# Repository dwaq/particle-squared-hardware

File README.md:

# Particle Squared - Bare Bones

This is a forked version of [Jared Wolff's Particle Squared Hardware](https://bitbucket.org/circuitdojo/particle-squared-hardware). For more information on that board, [visit his website](https://www.jaredwolff.com/particle-squared-air-quality-sensor/). To support him and his work, you can  [order his sensors from here](https://www.jaredwolff.com/store/particle-squared/).

Particle^2 (pronounced Particle Squared) is a circuit board that helps you monitor the air quality around you. I call my fork of the project "Bare Bones" because I removed the air particulate sensor. It can still monitor humidity, temperature, eCO2 and TVOCs.

I also made some minor changes to the project to suit my goals.

This project was designed using Autodesk Eagle.

The [Eagle-Renders](/Eagle-Renders) directory contains PDF and PNG renders of the schematic and board layout.

[Here is a shared project on Mouser for the BOM for one PCB.](https://www.mouser.com/ProjectManager/ProjectDetail.aspx?AccessID=5dd38de383)

## License

The license for these files is: [Attribution-ShareAlike 4.0 International](https://creativecommons.org/licenses/by-sa/4.0/). See included `LICENSE` file for all the legal stuff.

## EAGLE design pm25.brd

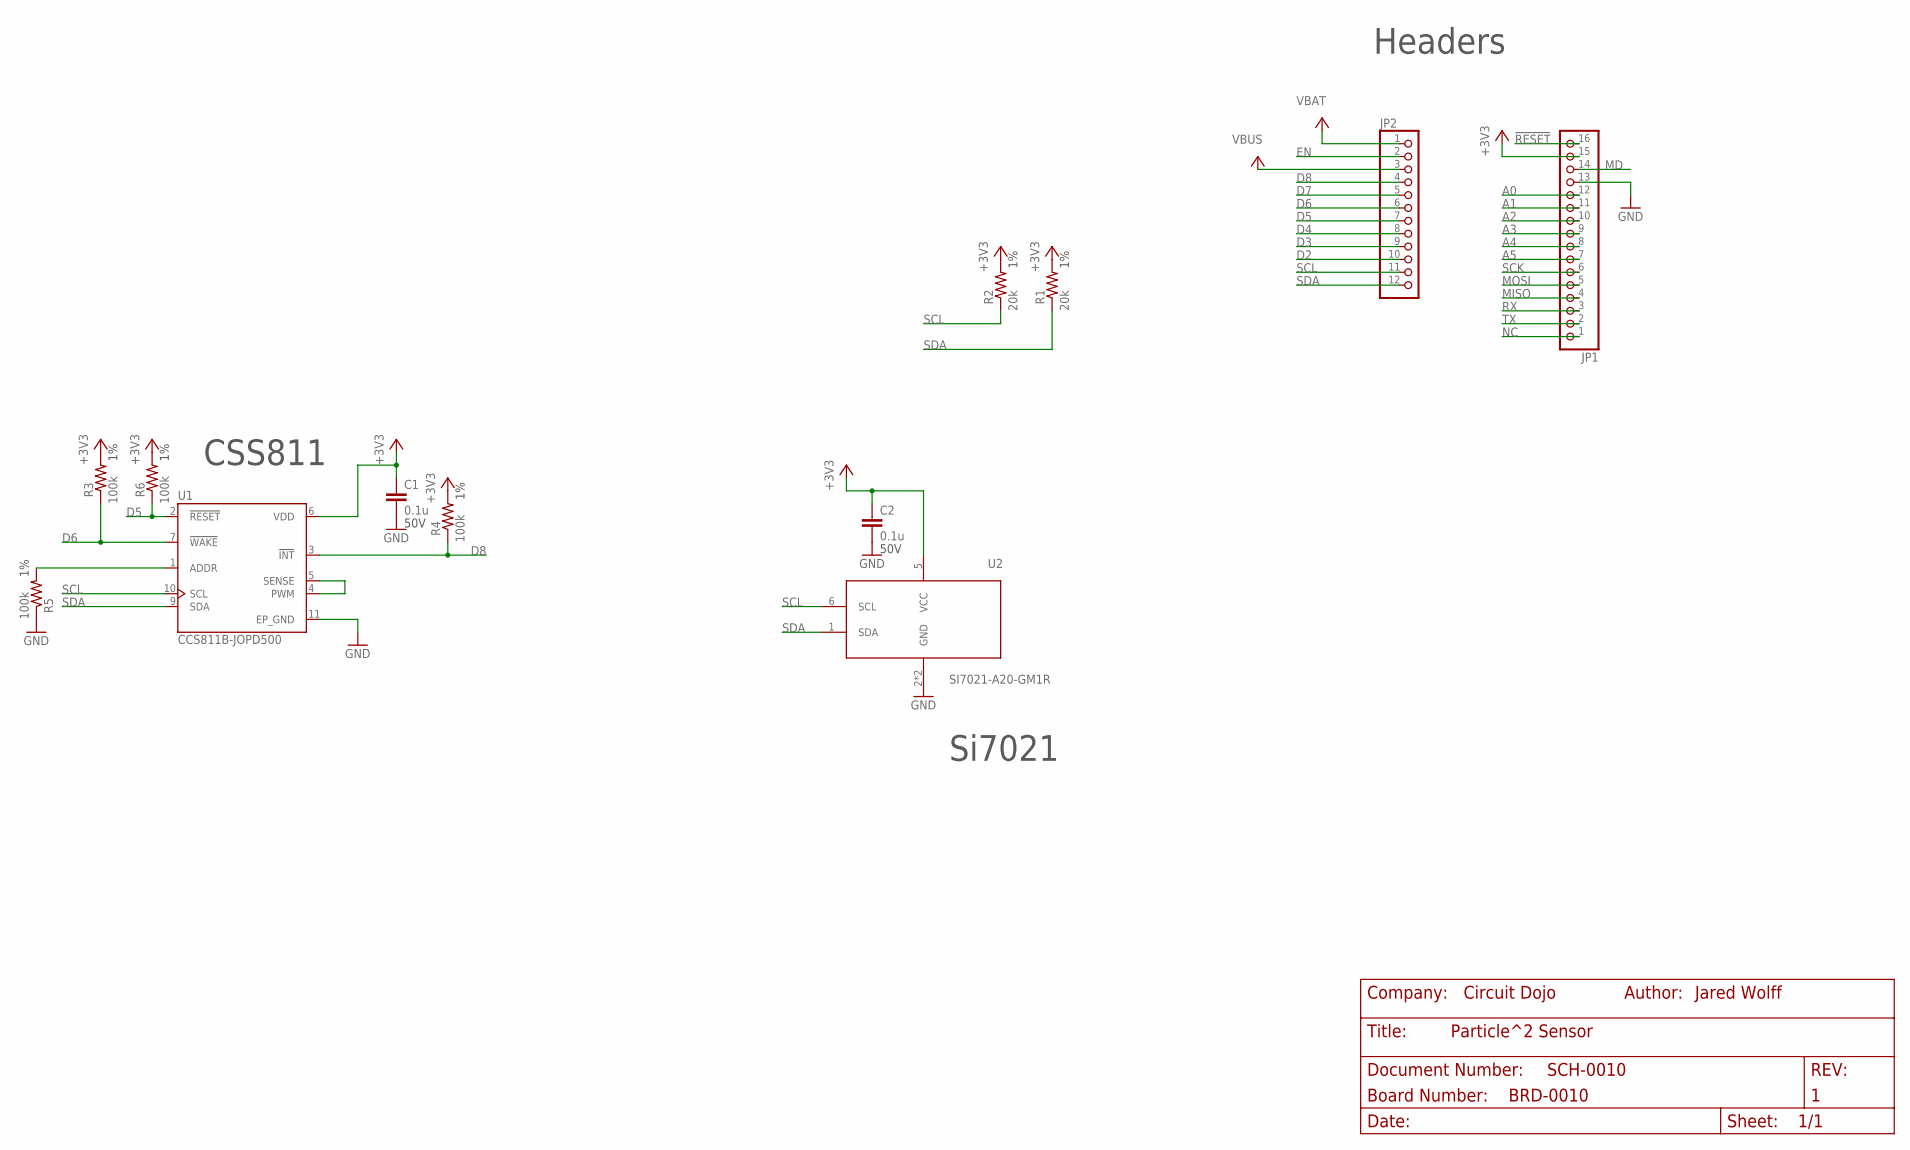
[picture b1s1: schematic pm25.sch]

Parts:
C1, C2: 0.1u; CAPC1005X55N
JP1: HEADER-1X16ROUND; 1X16_ROUND; MPN PPPC161LFBN-RC
JP2: HEADER-1X12; 1X12_ROUND; MPN PPPC121LFBN-RC
R1, R2: 20k; R0402
R3, R4, R5, R6: 100k; R0402
U1: CCS811B-JOPD500; SON60P400X270X110-11N
U2: SI7021-A20-GM1R; SON100P300X300X80-7N

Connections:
!RESET: JP1.16
+3V3: C1.1, C2.1, JP1.15, R1.2, R2.2, R3.2, R4.2, R6.2, U1.6 (VDD), U2.5 (VCC)
A0: JP1.12
A1: JP1.11
A2: JP1.10
A3: JP1.9
A4: JP1.8
A5: JP1.7
D2: JP2.10
D3: JP2.9
D4: JP2.8
D5: JP2.7, R6.1, U1.2 (!RESET)
D6: JP2.6, R3.1, U1.7 (!WAKE)
D7: JP2.5
D8: JP2.4, R4.1, U1.3 (!INT)
EN: JP2.2
GND: C1.2, C2.2, JP1.13, R5.1, U1.11 (EP_GND), U2.2 (GND), U2.7 (GND)
MD: JP1.14
MISO: JP1.4
MOSI: JP1.5
unnamed: R5.2, U1.1 (ADDR)
unnamed: U1.4 (PWM), U1.5 (SENSE)
NC: JP1.1
RX: JP1.3
SCK: JP1.6
SCL: JP2.11, R2.1, U1.10 (SCL), U2.6 (SCL)
SDA: JP2.12, R1.1, U1.9 (SDA), U2.1 (SDA)
TX: JP1.2
VBAT: JP2.1
VBUS: JP2.3

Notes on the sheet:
Si7021
CSS811
Headers

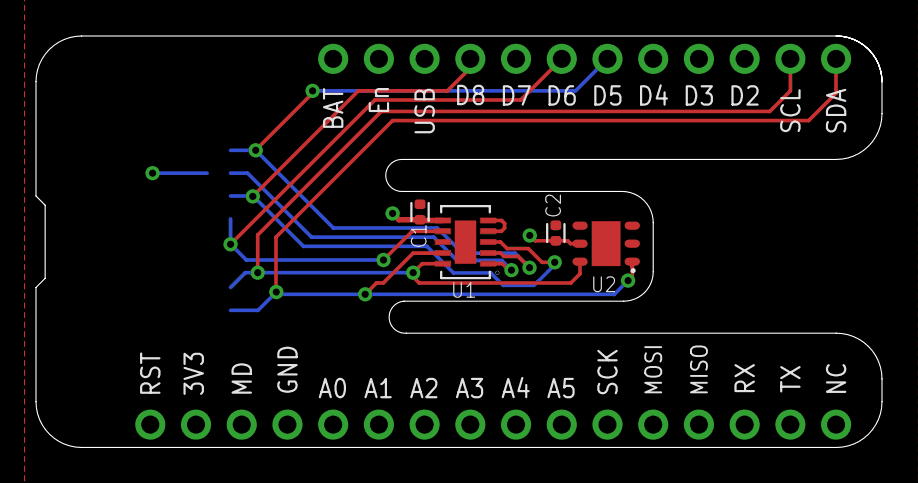
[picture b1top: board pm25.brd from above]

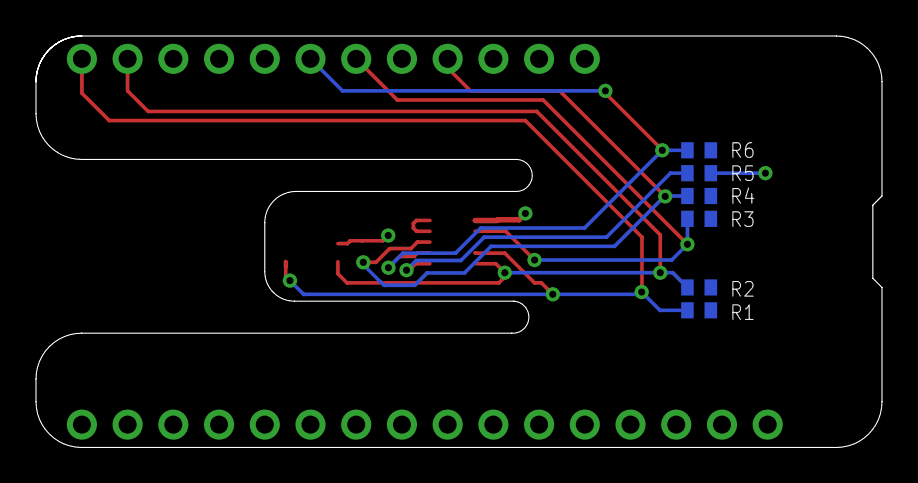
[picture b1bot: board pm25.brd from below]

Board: 2 copper layers, 47.0 x 22.9 mm, 12 parts (6 on the bottom side), 9 nets.

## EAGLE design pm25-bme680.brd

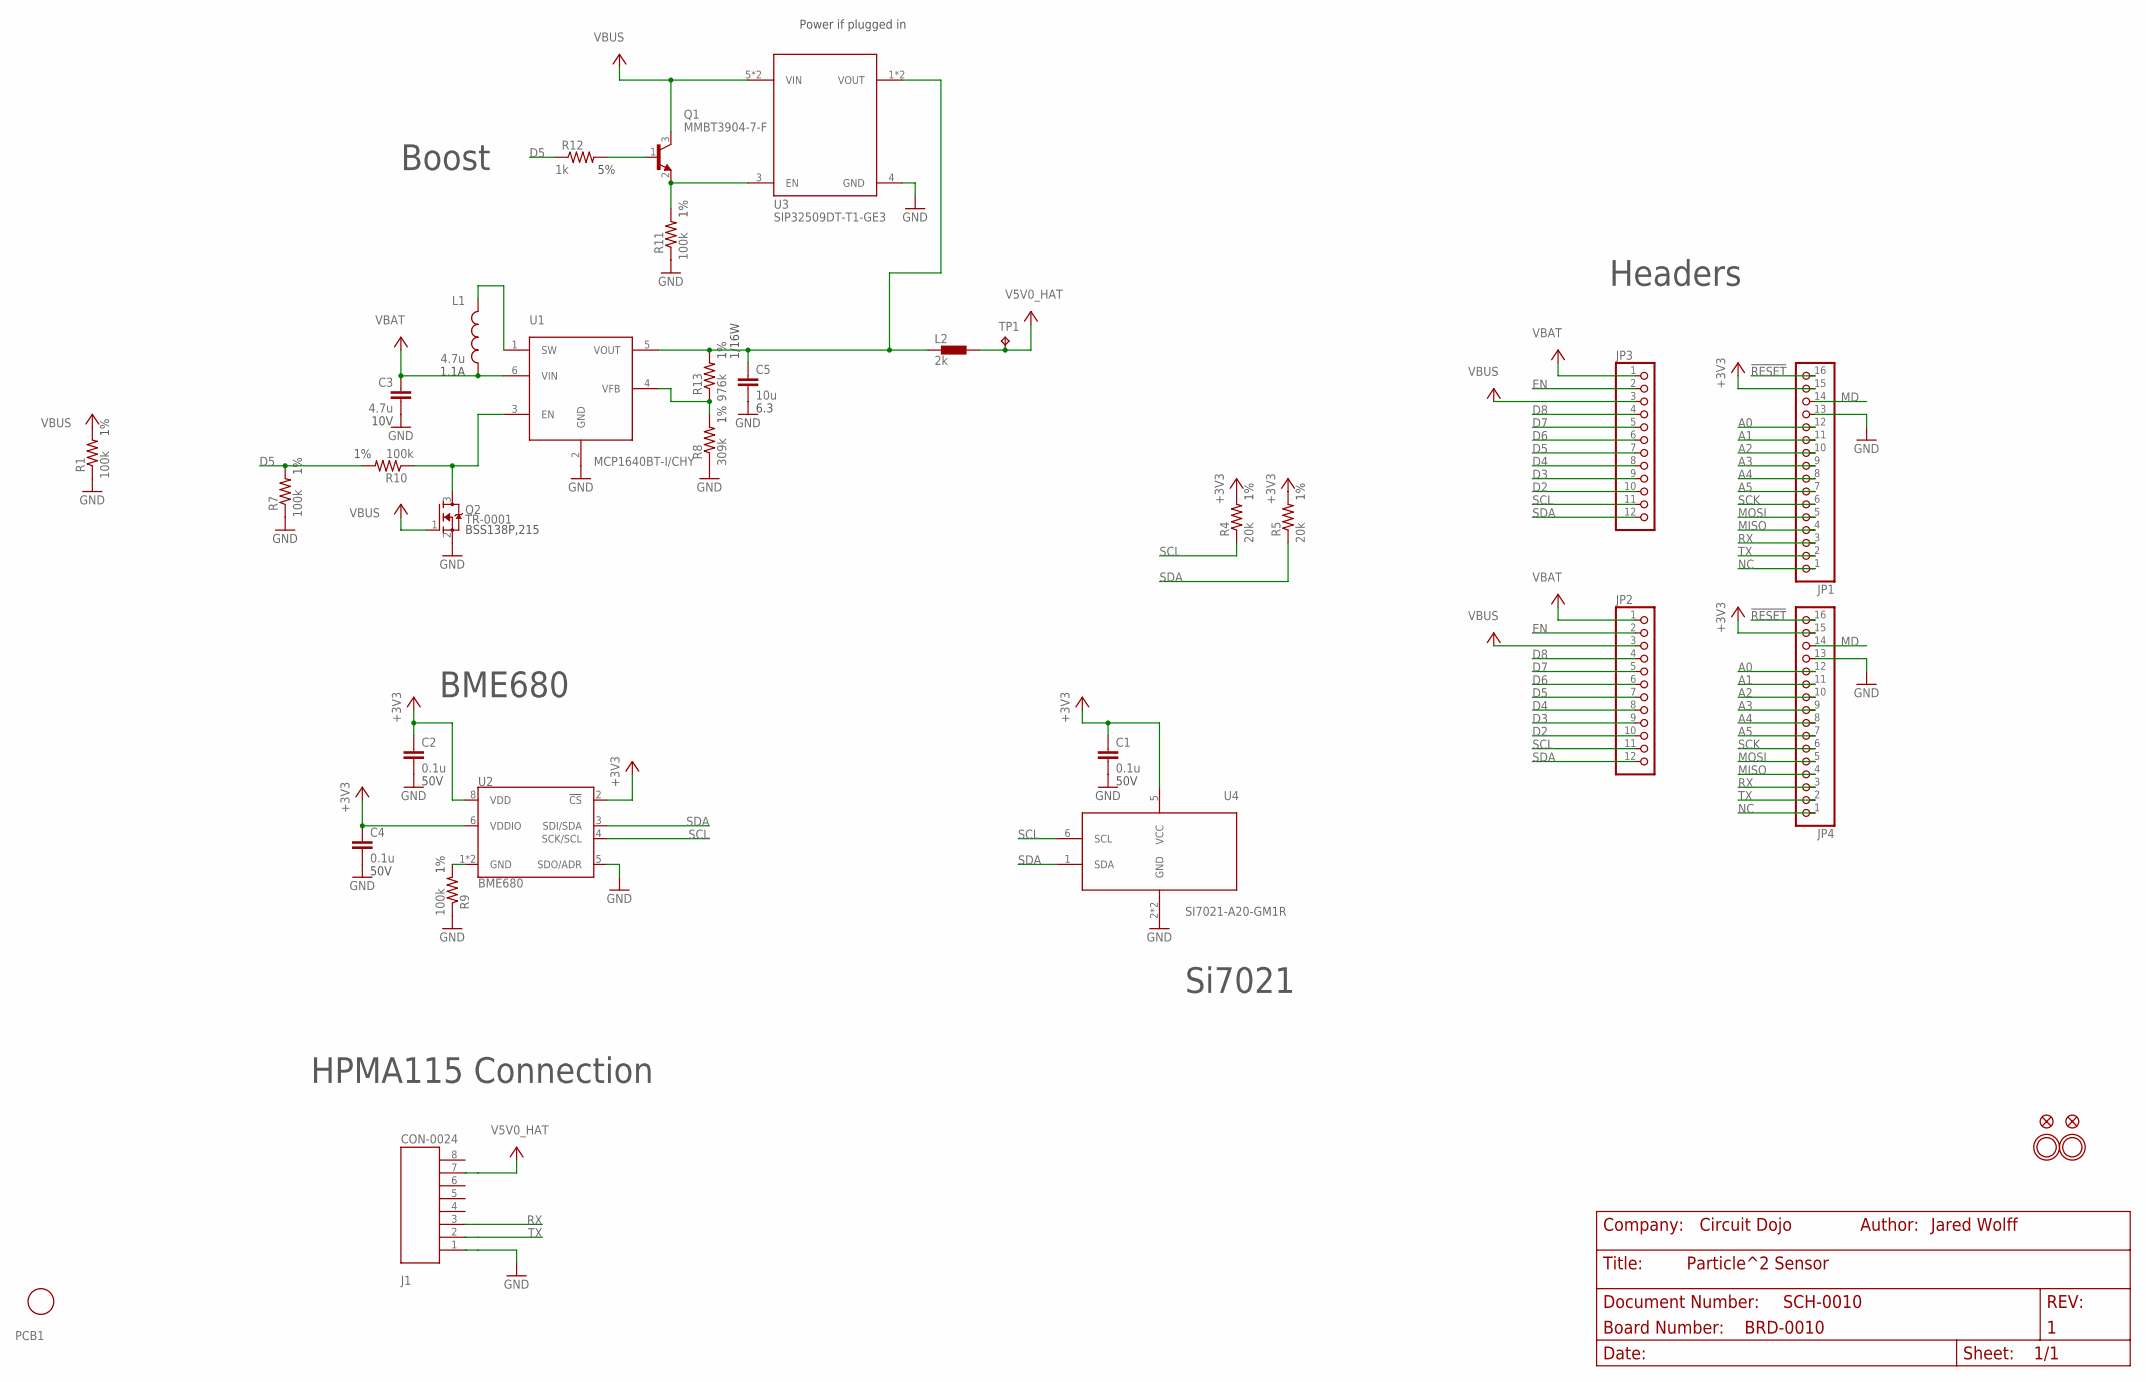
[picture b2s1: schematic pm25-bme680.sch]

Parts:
C1, C2, C4: 0.1u; CAPC1005X55N
C3: 4.7u; C0603
C5: 10u; C0603
J1: CON-0024; 0532610871
JP1: HEADER-1X16ROUND; 1X16_ROUND; MPN PPPC161LFBN-RC
JP2: HEADER-1X12; 1X12_ROUND
JP3: HEADER-1X12; 1X12_ROUND; MPN PPPC121LFBN-RC
JP4: HEADER-1X16ROUND; 1X16_ROUND
L1: 4.7u; IND-2P0X2P0X1P2
L2: 2k; R0805
PCB1: PCB-BME680-SI7021; PLACEHOLDER
Q1: TRANSISTOR-NPN-40V-0.2A-SOT23; SOT23
Q2: TR-0001; SOT23
R1, R7, R9, R10, R11: 100k; R0402
R4, R5: 20k; R0402
R8: 309k; R0402
R12: 1k; R0402
R13: 976k; R0402
TP1: TP; TP-1P27
U1: POWER-VREG-FB-EN-SW-350MA; SOT23-6
U2: BME680; LGA3.0X3.0
U3: POWER-SWITCH-SIP32509DT; SOT23-6
U4: SI7021-A20-GM1R; SON100P300X300X80-7N
U$31, U$32: MOUNTINGHOLE2.5; MOUNTINGHOLE_2.5_PLATED
U$34, U$35: FIDUCIAL""; FIDUCIAL_1MM

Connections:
!RESET: JP1.16, JP4.16
+3V3: C1.1, C2.1, C4.1, JP1.15, JP4.15, R4.2, R5.2, U2.2 (!CS), U2.6 (VDDIO), U2.8 (VDD), U4.5 (VCC)
A0: JP1.12, JP4.12
A1: JP1.11, JP4.11
A2: JP1.10, JP4.10
A3: JP1.9, JP4.9
A4: JP1.8, JP4.8
A5: JP1.7, JP4.7
D2: JP2.10, JP3.10
D3: JP2.9, JP3.9
D4: JP2.8, JP3.8
D5: JP2.7, JP3.7, R7.2, R10.2, R12.1
D6: JP2.6, JP3.6
D7: JP2.5, JP3.5
D8: JP2.4, JP3.4
EN: JP2.2, JP3.2
GND: C1.2, C2.2, C3.2, C4.2, C5.2, J1.1, JP1.13, JP4.13, Q2.2 (S), R1.1, R7.1, R8.1, R9.1, R11.1, U1.2 (GND), U2.5 (SDO/ADR), U3.4 (GND), U4.2 (GND), U4.7 (GND)
MD: JP1.14, JP4.14
MISO: JP1.4, JP4.4
MOSI: JP1.5, JP4.5
unnamed: L1.P$1 (1), U1.1 (SW)
unnamed: R8.2, R13.1, U1.4 (VFB)
unnamed: Q1.2 (E), R11.2, U3.3 (EN)
unnamed: R9.2, U2.1 (GND), U2.7 (GND)
unnamed: Q2.3 (D), R10.1, U1.3 (EN)
unnamed: Q1.1 (B), R12.2
NC: JP1.1, JP4.1
RX: J1.3, JP1.3, JP4.3
SCK: JP1.6, JP4.6
SCL: JP2.11, JP3.11, R4.1, U2.4 (SCK/SCL), U4.6 (SCL)
SDA: JP2.12, JP3.12, R5.1, U2.3 (SDI/SDA), U4.1 (SDA)
TX: J1.2, JP1.2, JP4.2
V5V0_BEAD: C5.1, L2.1, R13.2, U1.5 (VOUT), U3.1 (VOUT), U3.2 (VOUT)
V5V0_HAT: J1.7, L2.2, TP1.P$1, TP1.P$2, TP1.TP
VBAT: C3.1, JP2.1, JP3.1, L1.P$2 (2), U1.6 (VIN)
VBUS: JP2.3, JP3.3, Q1.3 (C), Q2.1 (G), R1.2, U3.5 (VIN), U3.6 (VIN)

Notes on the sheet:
Boost
Si7021
BME680
HPMA115 Connection
Headers
Power if plugged in

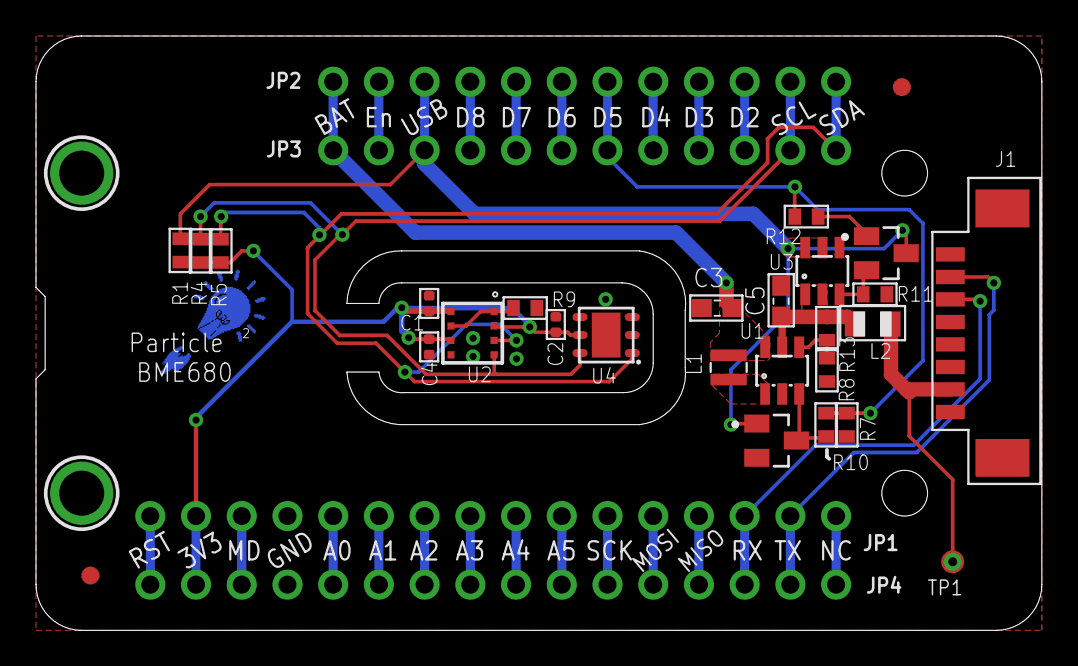
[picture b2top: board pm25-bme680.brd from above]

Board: 2 copper layers, 55.9 x 33.0 mm, 34 parts (0 on the bottom side), 36 nets.

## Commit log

2019-04-25 First commit. BME680 version.
2019-06-20 remove dust sensor and other extra circuitry
2019-06-21 made a cut out that extends to a smaller board size
2019-06-21 finally deleted those holes
2019-06-24 Shrink width to 0.9" standard
2019-06-24 roundover the central cutout
2019-06-24 Move pin label silkscreen from bottom to top
2019-06-24 Un-mirror text now that its on the top
2019-06-24 deleted one last piece of silkscreen
2019-06-24 rip up all traces outside of island
2019-06-24 Move resistors to bottom and align
2019-06-24 Huge reroute effort - not done yet
    Also replace pours: Top=GND, Bottom=+3V3
2019-06-24 Opened up the channel and improved the routing
2019-06-24 routing done but pours barely connect
2019-06-24 happy with the routing now
2019-06-24 rename the parts sequentially
2019-06-24 Move some silkscreen around
2019-06-24 remove logo from silkscreen
2019-06-24 more minor silkscreen changes
2019-06-24 line up all the pin names on silkscreen
2019-06-24 Gerbers for PCB ordered
2019-08-15 Remove outdated fritzing diagram
2019-08-15 Add details about my fork
2019-08-15 Export schematic as PDF and PNG (300dpi)
2019-08-15 Export board (standard/top/bottom) as PNG (300dpi)
2019-08-15 Export board (standard/top/bottom) as PDF
2019-08-15 Use Eagle's print to file function for schematic
2019-08-15 Move all PDFs and PNGs to new directory
2019-08-15 Include info about Eagle & Renders
2019-08-16 add link to Mouser BOM

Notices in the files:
parts and their libraries:
microbuilder: This work is placed in the public domain, and may be freely used for commercial and non-commercial work with the following conditions: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
